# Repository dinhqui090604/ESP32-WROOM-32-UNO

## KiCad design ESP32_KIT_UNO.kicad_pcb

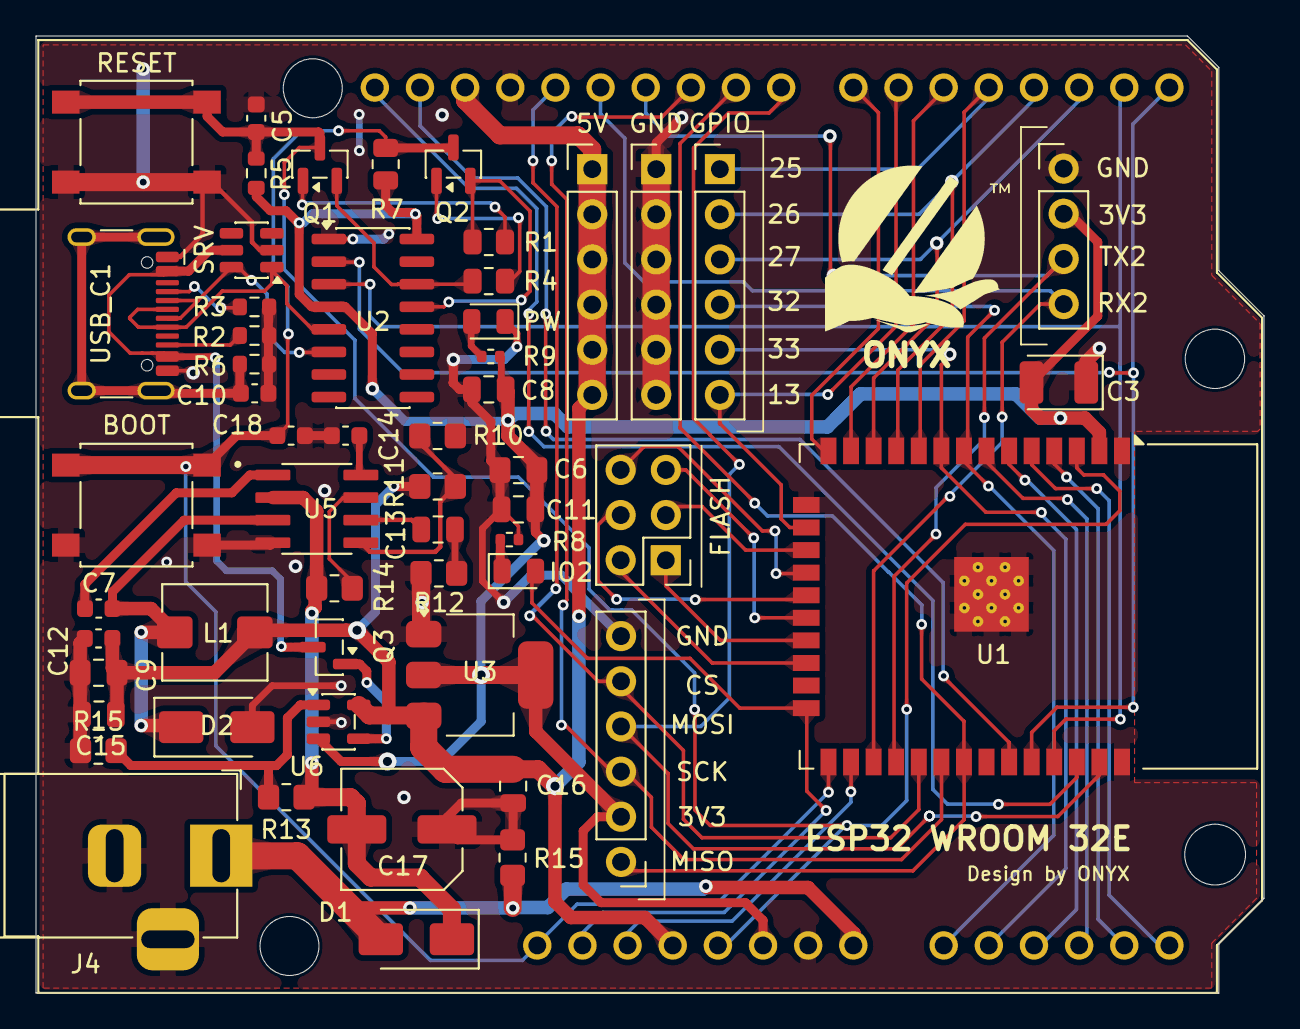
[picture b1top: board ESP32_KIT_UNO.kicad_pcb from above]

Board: 2 copper layers, 69.1 x 53.8 mm, 56 parts (0 on the bottom side), 58 nets.

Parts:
5V: Conn_01x06_Pin; PinHeader_1x06_P2.54mm_Vertical
BOOT: Boot; SW_SPST_B3S-1000
C3: 22uF; CP_EIA-3528-21_Kemet-B
C5, C14, C18: 0.1uF; C_0603_1608Metric
C6: 22uF; C_0805_2012Metric_Pad1.18x1.45mm_HandSolder
C7, C10: 10nF; C_0603_1608Metric
C8, C11, C15: 0.1uF; C_0805_2012Metric
C9: 10uF; C_0805_2012Metric_Pad1.18x1.45mm_HandSolder
C12: 22uF; C_0603_1608Metric
C13: 3.3nF; C_0805_2012Metric
C16: 10uF; C_0805_2012Metric
C17: 220uF; C_Elec_6.3x5.4
D1, D2: SS34; D_SMA
FLASH: PinHeader_2x03_P2.54mm_Vertical
GND: Conn_01x06_Pin; PinHeader_1x06_P2.54mm_Vertical
GPIO: Conn_01x06_Pin; PinHeader_1x06_P2.54mm_Vertical
IO2: BLUE; LED_0805_2012Metric
J4: Jack DC; BarrelJack_Horizontal
L1: 10uH; L_Bourns_SRP5030T
LAYOUT_UNO_R3: Arduino_UNO_R3; ESP32_LAYOUT_UNOR3
PW: LED; LED_0805_2012Metric
Q1, Q2: BC817; SOT-23
Q3: SOT-23
R1, R4, R7: 10k; R_0805_2012Metric
R2, R3: 5K1; R_0603_1608Metric
R5: 10k; R_0603_1608Metric
R6: 1M; R_0603_1608Metric
R8, R9: 1k; R_0402_1005Metric
R10: 10k; R_0805_2012Metric_Pad1.20x1.40mm_HandSolder
R11: 47k; R_0805_2012Metric_Pad1.20x1.40mm_HandSolder
R12: 5k6; R_0805_2012Metric_Pad1.20x1.40mm_HandSolder
R13, R14, R15, R15#2: 100k; R_0805_2012Metric_Pad1.20x1.40mm_HandSolder
RESET: Reset; SW_SPST_B3S-1000
SPI1: PinHeader_1x06_P2.54mm_Vertical
SRV: SOT-23-6
U1: ESP32-WROOM-32
U2: CH340C; SOIC-16_3.9x9.9mm_P1.27mm
U3: AMS1117-3.3; SOT-223-3_TabPin2
U5: MP1482DS-LF-Z; SOIC127P600X175-8N
U6: LMV321; SOT-23-5
UART2: Conn_01x04_Pin; PinHeader_1x04_P2.54mm_Vertical
USB_C1: USB_C; USB_C_Receptacle_HCTL_HC-TYPE-C-16P-01A

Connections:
+3.3V: C3.2, C6.2, C8.2, C11.2, LAYOUT_UNO_R3.6 (GND), R5.2, R7.2, R9.1, SPI1.2, U1.2 (VDD), U2.4 (V3), U2.16 (VCC), U3.2 (VO), U6.3 (-), UART2.2
/+5V: 5V.1, 5V.2, 5V.3, 5V.4, 5V.5, 5V.6, C9.2, C12.1, C15.2, C16.2, L1.2, LAYOUT_UNO_R3.4 (3V3), LAYOUT_UNO_R3.30 (AREF), Q3.2 (S), R11.1, U3.3 (VI), U6.5 (V+)
/CLK: FLASH.5, U1.20 (SCK/CLK)
/CMD: FLASH.4, U1.19 (SCS/CMD)
/DTR: Q2.2 (E), R1.1, U2.13 (~DTR)
/EN: C5.1, LAYOUT_UNO_R3.5 (+5V), Q1.3 (C), R5.1, RESET.1, U1.3 (EN)
/IO0: BOOT.1, C18.1, LAYOUT_UNO_R3.1 (IO0), Q2.3 (C), R7.1, U1.25 (IO0)
/IO2: IO2.2 (A), LAYOUT_UNO_R3.2 (IOREF), U1.24 (IO2)
/IO4: LAYOUT_UNO_R3.3 (~RESET), U1.26 (IO4)
/IO5: LAYOUT_UNO_R3.28 (D13), SPI1.5, U1.29 (IO5)
/IO12: LAYOUT_UNO_R3.22 (D7), U1.14 (IO12)
/IO13: GPIO.6, LAYOUT_UNO_R3.21 (D6), U1.16 (IO13)
/IO14: LAYOUT_UNO_R3.20 (D5), U1.13 (IO14)
/IO16_RX2: LAYOUT_UNO_R3.27 (D12), U1.27 (IO16), UART2.4
/IO17_TX2: LAYOUT_UNO_R3.26 (D11), U1.28 (IO17), UART2.3
/IO18: LAYOUT_UNO_R3.25 (D10), SPI1.3, U1.30 (IO18)
/IO19: LAYOUT_UNO_R3.24 (D9), SPI1.1, U1.31 (IO19)
/IO21: LAYOUT_UNO_R3.31 (SDA/A4), U1.33 (IO21)
/IO22: LAYOUT_UNO_R3.32 (SCL/A5), U1.36 (IO22)
/IO23: LAYOUT_UNO_R3.23 (D8), SPI1.4, U1.37 (IO23)
/IO25: GPIO.1, LAYOUT_UNO_R3.19 (D4), U1.10 (IO25)
/IO26: GPIO.2, LAYOUT_UNO_R3.18 (D3), U1.11 (IO26)
/IO27: GPIO.3, LAYOUT_UNO_R3.17 (D2), U1.12 (IO27)
/IO32: GPIO.4, LAYOUT_UNO_R3.9 (A0), U1.8 (IO32)
/IO33: GPIO.5, LAYOUT_UNO_R3.10 (A1), U1.9 (IO33)
/IO34: LAYOUT_UNO_R3.11 (A2), U1.6 (IO34)
/IO35: LAYOUT_UNO_R3.12 (A3), U1.7 (IO35)
/RTS: Q1.2 (E), R4.2, U2.14 (~RTS)
/RXD: LAYOUT_UNO_R3.15 (D0/RX), U1.34 (RXD0/IO3), U2.2 (TXD)
/SD0: FLASH.1, U1.21 (SDO/SD0)
/SD1: FLASH.2, U1.22 (SDI/SD1)
/SD2: FLASH.3, U1.17 (SHD/SD2)
/SD3: FLASH.6, U1.18 (SWP/SD3)
/TXD: LAYOUT_UNO_R3.16 (D1/TX), U1.35 (TXD0/IO1), U2.3 (RXD)
/VIN: D1.2 (A), J4.1, LAYOUT_UNO_R3.8 (VIN), R15.1
/VN: LAYOUT_UNO_R3.14 (SCL/A5), U1.5 (SENSOR_VN)
/VP: LAYOUT_UNO_R3.13 (SDA/A4), U1.4 (SENSOR_VP)
GND: BOOT.2, C3.1, C5.2, C6.1, C8.1, C9.1, C10.2, C11.1, C12.2, C14.1, C15.1, C16.1, C17.1, C18.2, D2.2 (A), GND.1, GND.2, GND.3, GND.4, GND.5, GND.6, J4.2, J4.3, LAYOUT_UNO_R3.7 (GND), LAYOUT_UNO_R3.29 (GND), PW.1 (K), R2.2, R3.2, R6.1, R8.2, R10.1, R12.2, R15.2, R15#2.1, RESET.2, SPI1.6, SRV.2 (VN), U1.1 (GND), U1.15 (GND), U1.38 (GND), U1.39 (GND), U2.1 (GND), U3.1 (GND), U5.4 (GND), U6.2 (V-), UART2.1, USB_C1.A1 (GND), USB_C1.A12 (GND), USB_C1.B1 (GND), USB_C1.B12 (GND)
unnamed: Q3.1 (G), U6.4
unnamed: IO2.1 (K), R8.1
unnamed: C13.1, R12.1
unnamed: C17.2, D1.1 (K), R13.2, R14.1, U5.2 (IN)
unnamed: C7.2, D2.1 (K), L1.1, U5.3 (SW)
unnamed: Q1.1 (B), R1.2
unnamed: Q2.1 (B), R4.1
unnamed: PW.2 (A), R9.2
unnamed: SRV.1 (IO1), U2.5 (UD+), USB_C1.A6 (D+), USB_C1.B6 (D+)
unnamed: SRV.6 (IO4), U2.6 (UD-), USB_C1.A7 (D-), USB_C1.B7 (D-)
unnamed: C7.1, U5.1 (BS)
unnamed: C13.2, U5.6 (COMP)
unnamed: R14.2, U5.7 (EN)
unnamed: R10.2, R11.2, U5.5 (FB)
unnamed: C14.2, U5.8 (SS)
unnamed: R13.1, R15#2.2, U6.1 (+)
unnamed: R3.1, USB_C1.A5 (CC1)
unnamed: R2.1, USB_C1.B5 (CC2)
unnamed: C10.1, R6.2, USB_C1.SH (SHIELD)
VBUS: Q3.3 (D), SRV.5 (VP), USB_C1.A4 (VBUS), USB_C1.A9 (VBUS), USB_C1.B4 (VBUS), USB_C1.B9 (VBUS)

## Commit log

2026-05-29 Khởi tạo dự án
2026-06-02 Cap nhat file thiet ke KiCad va xuat file Gerber PDF
